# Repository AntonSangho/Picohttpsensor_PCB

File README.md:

# 피코보드 

## 진행상황 
- [x] 회로 설계
- [x] 레이아웃 설계 
- [x] PCB 제작
- [ ] PCB 주문

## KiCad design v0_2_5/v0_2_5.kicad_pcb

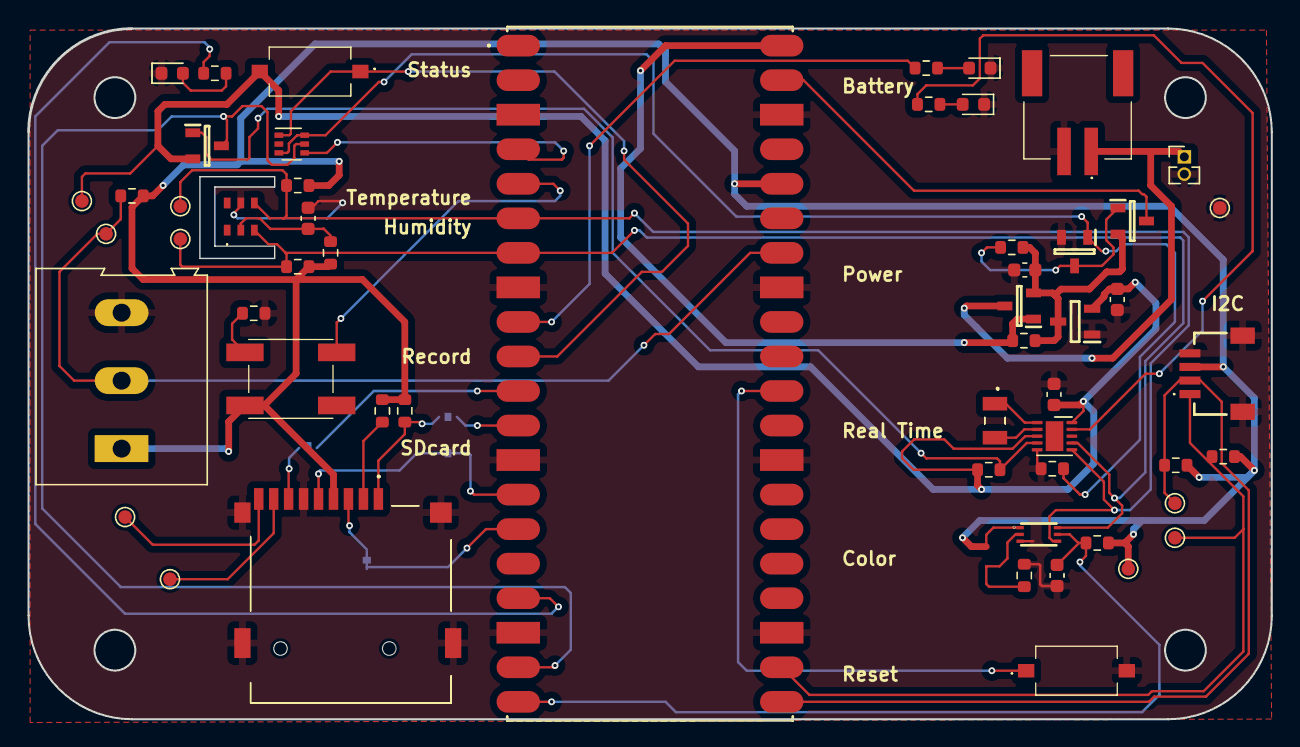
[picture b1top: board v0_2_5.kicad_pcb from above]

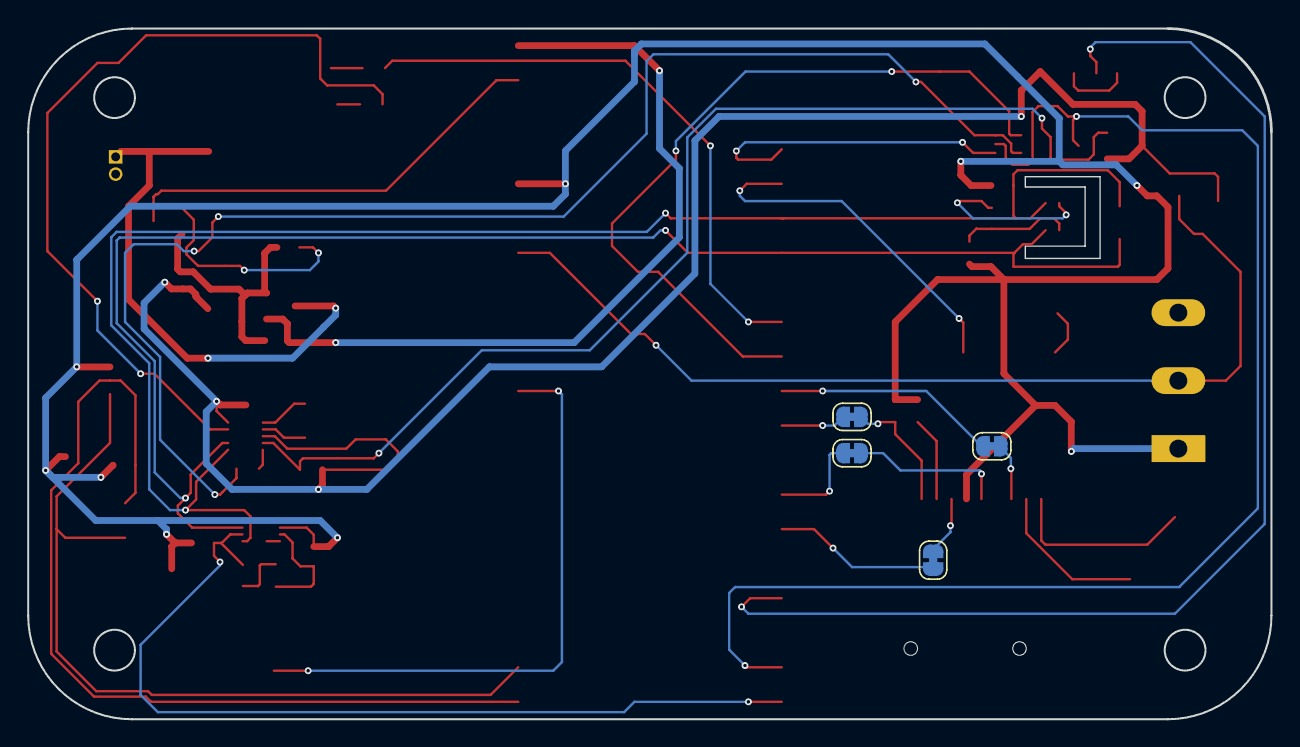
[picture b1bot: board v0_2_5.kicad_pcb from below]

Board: 2 copper layers, 91.4 x 50.8 mm, 59 parts (4 on the bottom side), 41 nets.

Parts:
C1, C3, C4, C6: 1uF; C_0603_1608Metric
C5: 0.1uF; C_0603_1608Metric
D1: WhiteLED; LED_0603_1608Metric
D2, D4: RedLED; LED_0603_1608Metric
D3: 1PS88SB48; SOT-363_SC-70-6
IC1: RASPBERRY_PI_PICO_W; RASPBERRYPIPICOW
IC2: BH1750FVI-TR; WSOF6
IC3: AP2138N-3.3TRG1; SOT95P282X145-3N
J1: S2B-PH-SM4-TB_LF__SN_; S2BPHSM4TBLFSN
J3: TF-115; TF115
J4: SM04B-SRSS-TB; SM04BSRSSTB
J5: Screw_Terminal_01x03; TerminalBlock_Altech_AK300-3_P5.00mm
J6: Conn_01x02_Pin; PinHeader_1x02_P1.27mm_Vertical
JP2, JP3, JP4, JP8: Jumper_2_Bridged; SolderJumper-2_P1.3mm_Bridged_RoundedPad1.0x1.5mm
Q1, Q2, Q3: DMG2301L-7; SOT96P240X110-3N
Q5: DMN3731U-7; SOT96P240X110-3N
R1, R2, R16: 120K; R_0603_1608Metric
R3, R4, R5, R6, R13, R20: 10K; R_0603_1608Metric
R7, R8, R11, R17: 1K; R_0603_1608Metric
R9, R10: 47K; R_0603_1608Metric
R12: 220; R_0603_1608Metric
R14: 4K7; R_0603_1608Metric
R15: 620K; R_0603_1608Metric
S1, S2: TS-1101-C-W; TS1101CW
S4: SKHUAKE010
TP1, TP2, TP3, TP4, TP5, TP6, TP9, TP10, TP11, TP12: TestPoint; TestPoint_Pad_D1.0mm
U1: AHT20
U2: PCF85063ATL; DFN-10-1EP_2.6x2.6mm_P0.5mm_EP1.3x2.2mm
Y1: Q13FC1350000200

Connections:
+3.3V: IC1.36 (3V3(OUT)), IC2.1 (VCC), J3.4 (VDD), J4.3, J5.1, R3.2, R4.2, R5.2, R6.2, R8.2, R9.1, R10.1, R12.2, R14.1, S4.2, TP9.1
+BATT: J1.1, J6.1, Q1.3
/ACT_LED: IC1.9 (I2C1_SDA_/SPI0_SCK/GP6), R7.1
/ALARM_LED: R17.1, U2.9 (CLKOUT)
/Button: IC1.5 (I2C0_SCL_/SPI0_TX/GP3), S4.3
/CS: IC1.12 (UART1_RX/I2C0_SCL_/SPI1_CSN/GP9), JP4.1 (A)
/DQ: IC1.34 (GP28/ADC2), J5.2, R14.2, TP12.1
/HOLD_VSYS_EN: D3.4 (A2), IC1.4 (I2C1_SDA_/SPI0_SCK/GP2)
/I2C0_SCL: IC1.22 (UART0_RX/I2C0_SCL/SPIO_CSN/GP17), J4.1, R4.1, TP1.1
/I2C0_SDA: IC1.21 (UART0_TX/I2C0_SDA_/SPI0_RX_/GP16), J4.2, R5.1, TP2.1
/I2C1_SCL: IC1.7 (UART1_RX/I2C0_SCL_/SPI0_CSN/GP5), IC2.6 (SCL), R3.1, TP3.1, U1.3 (SCL), U2.7 (SCL)
/I2C1_SDA: IC1.6 (UART1_TX/I2C0_SDA_/SPI0_RX/GP4), IC2.4 (SDA), R6.1, TP4.1, U1.4 (SDA), U2.6 (SDA)
/LDO/VIN: C3.1, IC3.3 (VIN), Q1.2, Q2.2, R1.2, R16.1
/MISO: IC1.11 (UART1_TX/I2C0_SDA_/SPI1_RX/GP8), JP3.1 (A)
/MOSI: IC1.15 (I2C1_SCL_/SPI1__TX/GP11), J3.3 (CMD), JP8.1 (A), JP8.2 (B)
/RESET: C6.1, IC1.20 (I2C1_SCL/SPI1_TX/GP15), IC2.5 (DVI), R8.1
/RTC_ALARM: D3.5 (A2), IC1.19 (I2C1_SDA/SPI1_SCK/GP14), Q3.3
/RUN: IC1.30 (RUN), S1.1 (COM)
/Record: IC1.17 (UART0_RX/I2C0_SCL_/SPI1_CSN/GP13), R11.1
/SCK: IC1.14 (I2C1_SDA_/SPI1__SCK/GP10), J3.5 (CLX), JP2.1 (A), JP2.2 (B)
/SDcard/CARDDET: J3.1 (DAT2), JP4.2 (B), R9.2
/SWITCH_STATUS: D3.1 (A1), IC1.10 (I2C1_SCL_/SPI0_TX/GP7), S2.1 (COM)
/VSYS_EN: D3.3 (K2), D3.6 (K1), Q5.1, R15.2
GND: C1.2, C3.2, C4.2, C5.2, C6.2, D1.1 (K), D2.1 (K), D4.1 (K), IC1.3 (GND_1), IC1.8 (GND_2), IC1.13 (GND_3), IC1.18 (GND_4), IC1.23 (GND_5), IC1.28 (GND_6), IC1.33 (GND/AGND), IC1.38 (GND_7), IC2.3 (GND), IC3.1 (GND), J1.2, J3.6 (VSS), J3.MP1, J3.MP2, J3.MP3, J3.MP4, J4.4, J4.MP1, J4.MP2, J5.3, J6.2, Q5.2, R13.1, R15.1, R20.1, S1.2 (NO), TP10.1, U1.5 (GND), U2.5 (VSS)
unnamed: D1.2 (A), R7.2
unnamed: D2.2 (A), R17.2
unnamed: D4.2 (A), R11.2
unnamed: IC2.2 (ADDR), R20.2
unnamed: J3.2 (CD/DAT3), R10.2
unnamed: J3.7 (DAT0), JP3.2 (B)
unnamed: J3.8 (DAT1), TP5.1
unnamed: J3.CD1, TP6.1
unnamed: Q2.1, Q5.3, R1.1
unnamed: R13.2, S4.4
unnamed: C5.1, R12.1, U1.2 (VDD)
unnamed: U2.1 (OSCI), Y1.1
unnamed: U2.2 (OSCO), Y1.2
unnamed: Q3.1, R2.2, U2.4 (~INT)
V+_A0: C1.1, C4.1, IC3.2 (VOUT), Q3.2, R2.1, S2.2 (NO), TP11.1, U2.3 (CLKOE), U2.10 (VDD)
VBUS: IC1.40 (VBUS), Q1.1, R16.2
VSYS: IC1.39 (VSYS), Q2.3

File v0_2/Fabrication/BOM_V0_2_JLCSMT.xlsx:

Comment | Designator | Footprint | JLCPCB Part #（optional）
MountingHole_Pad | H4,H1,H2,H3 | MountingHole_2.2mm_M2_Pad_TopBottom
HYCW110-TF10-180B | J2 | HYCW110TF10180B
RedLED | D2 | LED_0603_1608Metric
Q13FC1350000200 | Y1 | Q13FC1350000200
10K | R4,R13,R18,R14,R6,R3,R5,R20 | R_0603_1608Metric
120K | R16,R2,R1 | R_0603_1608Metric
1uF | C4,C1,C3,C6 | C_0603_1608Metric
1K | R8,R17,R7 | R_0603_1608Metric
DMG2301L-7 | Q3,Q2,Q1 | SOT96P240X110-3N
AP2138N-3.3TRG1 | IC3 | SOT95P282X145-3N
0.1uF | C5 | C_0603_1608Metric
AHT20 | U1 | AHT20
SolderJumper_2_Open | JP1 | SolderJumper-2_P1.3mm_Open_TrianglePad1.0x1.5mm
DMN3731U-13 | Q4 | SOT96P240X110-3N
WhiteLED | D1 | LED_0603_1608Metric
TS-1101-C-W | S2,S1 | TS1101CW
47K | R9,R10 | R_0603_1608Metric
Conn_01x09_Pin | J3 | PinHeader_1x09_P1.27mm_Vertical
220 | R12 | R_0603_1608Metric
1PS88SB48 | D3 | SOT-363_SC-70-6
PCF85063ATL | U2 | DFN-10-1EP_2.6x2.6mm_P0.5mm_EP1.3x2.2mm
BH1750FVI-TR | IC2 | WSOF6
620K | R15 | R_0603_1608Metric
RASPBERRY_PI_PICO_W | IC1 | RASPBERRYPIPICOW
S2B-PH-SM4-TB_LF__SN_ | J1 | S2BPHSM4TBLFSN

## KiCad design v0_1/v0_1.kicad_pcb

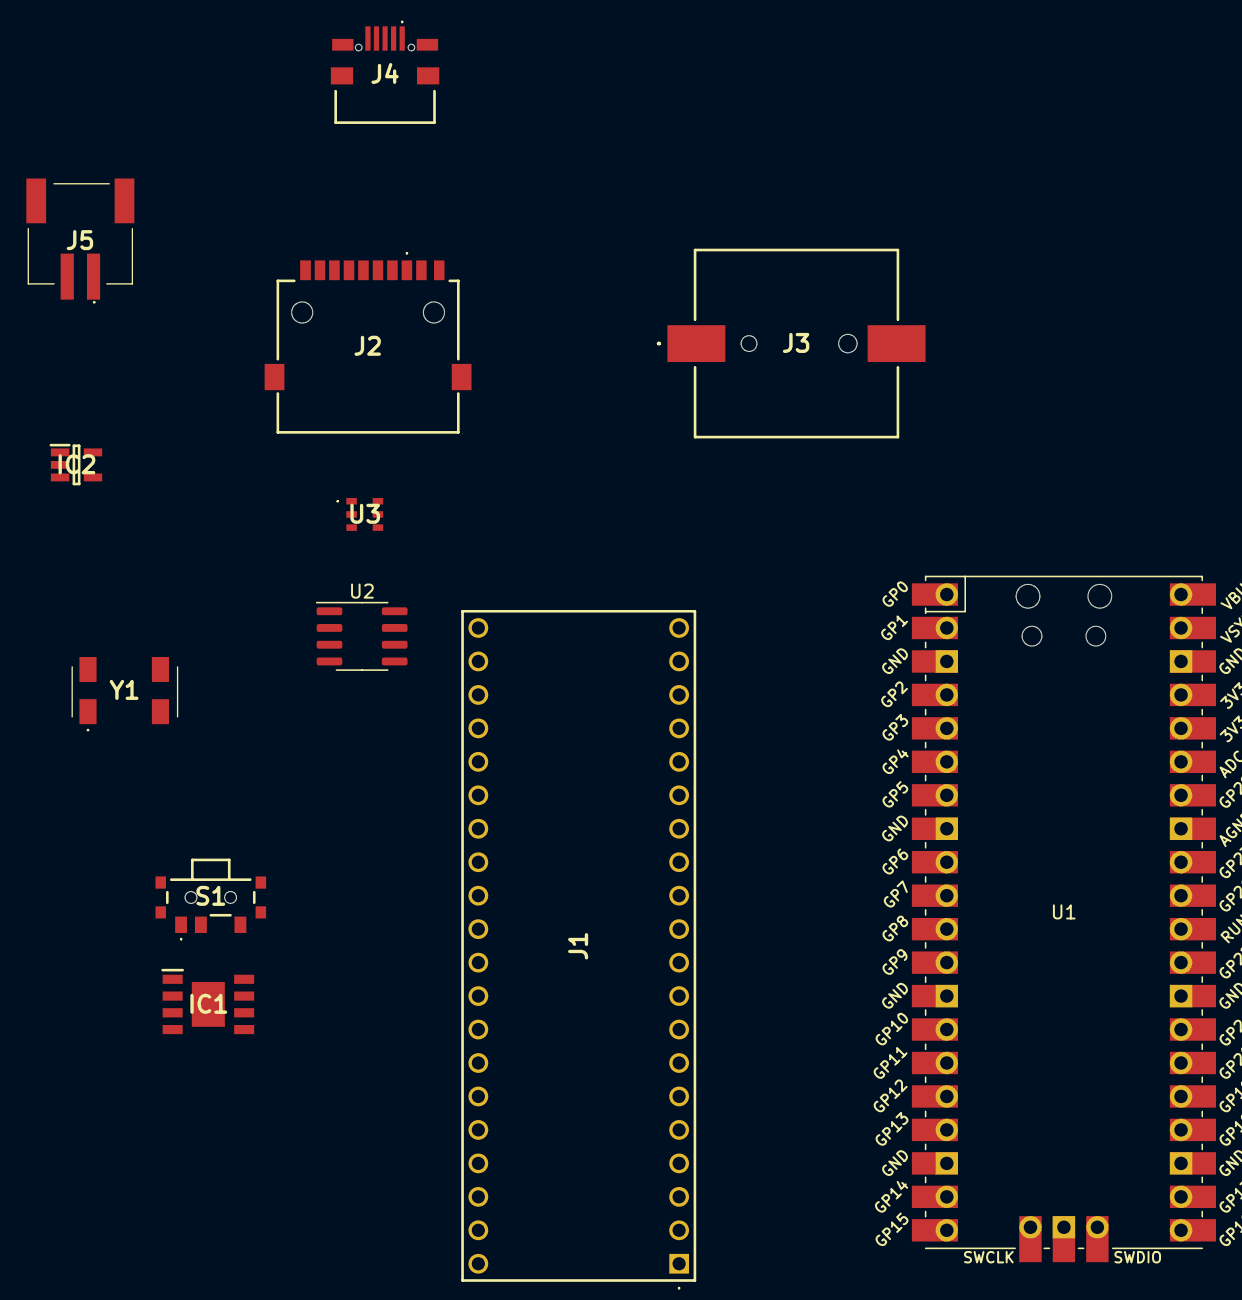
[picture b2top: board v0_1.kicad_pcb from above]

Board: 2 copper layers, 12 parts (0 on the bottom side), 8 nets, no tracks yet.

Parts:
IC1: TP4056-42-ESOP8; SOIC127P600X175-9N
IC2: MCP73831T-2ACI_OT; SOT95P270X145-5N
J1: Z-ICS0S40P-W000; ZICS0S40PW000
J2: HYCW110-TF10-180B; HYCW110TF10180B
J3: BS-12-B3AA009; BS12B3AA009
J4: MICROQTJ
J5: S2B-PH-SM4-TB_LF__SN_; S2BPHSM4TBLFSN
S1: MK-12C02-G020; MK12C02G020
U1: Pico; RPi_Pico_SMD_TH
U2: PCF8523T; SOIC-8_3.9x4.9mm_P1.27mm
U3: AHT20
Y1: MC-306_32.7680K-A0_ROHS; MC306327680KA5ROHS

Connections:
+3.3V: IC2.4 (VDD), J4.1, U1.36 (3V3)
GND: IC2.2 (VSS), J2.6 (VSS), J2.G1 (GROUND_1), J2.G2 (GROUND_2), J3.1 (-), J4.5, J5.1, U1.3 (GND), U1.8 (GND), U1.13 (GND), U1.18 (GND), U1.23 (GND), U1.28 (GND), U1.38 (GND), U2.4 (VSS)
unnamed: IC1.4 (VCC), IC1.8 (CE)
unnamed: IC2.3 (VBAT), J5.2
unnamed: J3.2 (+), U2.3 (VBAT)
unnamed: U2.1 (OSCI), Y1.4 (CRYSTAL_2)
unnamed: U2.2 (OSCO), Y1.1 (CRYSTAL_1)
VCC: J2.4 (VDD), U3.2 (VDD)

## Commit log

2023-09-19 add kicad files
2023-09-19 add gitignore
2023-09-19 add aht20
2023-09-19 change file name
2023-09-19 add charger ic
2023-09-19 add battery case
2023-09-19 slide switch
2023-09-19 save
2023-09-21 charger ic circuit
2023-09-21 add rtc and charger schematic
2023-09-22 add 0.2V
2023-09-25 change directory
2023-09-25 add sensor schematic
2023-09-25 add color sensor
2023-09-26 schematic for enviro done
2023-09-27 all part are added
2023-10-05 add sdcard socket
2023-10-05 for quoate
2023-10-06 rename i2c and add button
2023-10-07 add Altoids outline
2023-10-07 add altoids case
2023-10-10 add name and button part
2023-10-16 add part for TDS and watersensor
2023-10-23 power line
2023-10-23 new replacement v2.5
2023-10-23 add label
2023-10-27 route almost done:
2023-10-27 replacement
2023-11-02 change placement
2023-11-03 done
2023-11-04 change for manufacture
2023-11-06 replace sdcard
2023-11-10 add production file
2023-11-10 add img
2023-11-10 readme
